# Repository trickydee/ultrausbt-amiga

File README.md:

# Amiga USB & Bluetooth Adapter

## Overview

This project uses a Raspberry Pi Pico to connect modern USB and Bluetooth devices such as keyboards, mice, trackballs and gamepads to classic Amiga computers — without needing a USB stack on the Amiga itself.

The project was created so I could connect my modern peripherals with my Amiga 2000, the device has a Keyboard and 2 x Atari style Joystick connectors to interface with the Amiga.

The example adapter hardware for the project is focused on the Amiga 2000, although it can be adapted easily for other Amigas.

The adapter is bi-directional:

* **Device Mode** (default): modern USB/Bluetooth HID → Amiga keyboard, mouse, joystick, and CD32 pad signalling
* **Host Mode**: real Amiga keyboard + Port 1 mouse + Port 2 Atari stick → USB HID keyboard/mouse/gamepad on a modern PC

Joystick/CD32 pads are supported toward the Amiga in Device Mode. In Host Mode, Port 2 accepts an Atari-style two-button stick as a USB HID gamepad (Mega Drive pads deferred — see [`doc/host-mode-port2-joystick.md`](./doc/host-mode-port2-joystick.md)).

The device is connected to the Amiga using straight through cables, I am using 2 x 9 Pin DSub to Dsub and 1 x 5 Pin DIN (MIDI) cables.

On a **Pico 2 W** you can mix USB and Bluetooth devices. USB-only builds work on any Pico / Pico 2.

**This project is a fork of [amigahid-pico](https://github.com/borb/amigahid-pico)** by **just nine** (borb). That project is the foundation for Amiga keyboard and mouse signalling on the Pico. This fork builds on that work for the ultrausbt Amiga Adapter board: OLED UI, dual joystick ports, CD32 pad protocol, Bluetooth (Bluepad32), many modern USB controllers, and USB **device** mode (Amiga keyboard/mouse → PC).

Please visit and star the upstream project:  
**https://github.com/borb/amigahid-pico**

Current test firmware: **v4.3.0** (shared Bluepad32 reconnect PR testing; not yet released) · [Release notes](./RELEASE_NOTES.md) · Architecture: [`doc/architecture.md`](./doc/architecture.md) · License: [EPL-2.0](./LICENSE) · [NOTICE](./NOTICE)

## Contributions

This project is open source and I am happy to receive pull requests and issues to further improve capabilities.

## USB device support

* USB HID Keyboards
* USB HID Mice
* USB HID Gamepads / Joysticks (see below)

## Game controller support

The following USB HID gamepads / joysticks are supported (more to come):

* PlayStation 3 DualShock 3 (and third-party PS3-compatible pads: HORI, Mad Catz, Qanba, Nacon, Logitech F310, etc.)
* PlayStation 4 DualShock 4 (and third-party PS4-compatible pads)
* PlayStation 5 DualSense and DualSense Edge (USB)
* PlayStation Classic (PSC)
* Xbox XInput — Xbox 360 / One / OG (plus HID fallback)
* Nintendo Switch Pro Controller, Joy-Con (L/R/Pair/Grip), SNES Controller (NSO)
* HORI HORIPAD for Nintendo Switch
* Google Stadia Controller

Other USB HID gamepads may work via the generic path (directions + up to three buttons). Gamepads map to **Joystick Port 2** by default; Port 1 can be switched to joystick / Llamatron / CD32 mode from the OLED or keyboard shortcuts.

## Bluetooth support (Pico 2 W)

Bluetooth keyboards, mice, and gamepads are supported on the **Raspberry Pi Pico 2 W** (RP2350) via [Bluepad32](https://github.com/ricardoquesada/bluepad32). You can run a fully wireless Amiga setup, or mix USB and Bluetooth devices.

### Pairing

1. On the OLED splash screen, hold **Middle + Left** (# + Up) to enable pairing (or wait for the short post-boot pairing window).
2. Put your device into Bluetooth pairing mode.
3. Confirm the device on the OLED **Devices** / **Map Devices** screens.

To clear stored pairing keys, open the OLED **Settings** page on the screen carousel (`#` from Map Devices), select **Clear BT pair**, confirm with `#`.

To turn pairing back on after it has timed out or been turned off: **Settings → Pair ON** (or **Middle + Left** / # + Up on Splash).

**Note:** Bluetooth support is intended for Pico 2 W. Prefer Pico 2 W for wireless builds.

# Usage

## USB

Connect devices to the Pico USB port (use a powered USB OTG hub if you need multiple devices). Supported keyboards, mice, and gamepads should enumerate within a few seconds; confirm on the OLED. If you find a modern device that does not work, open an issue.

## Bluetooth

See **Bluetooth support** above. Pairing is controlled from the OLED splash screen. Keyboard shortcuts work the same on USB and Bluetooth keyboards.

## Keyboard shortcuts

The adapter uses a number of Keyboard shortcut key combinations to toggle features.

These combos are handled by the adapter (USB **and** Bluetooth keyboards) and are **not** passed through to the Amiga. **Left Amiga** = Left Command / Left GUI / Left Windows on PC/Mac keyboards.

| Shortcut | Function |
|----------|----------|
| **Ctrl + Left Amiga + Right Amiga** | Amiga hard reset (classic) |
| **Ctrl + Left Amiga + Backspace** | Amiga hard reset (alternate for keyboards without Right Amiga/GUI) |
| **Shift + Left Amiga + J** | Toggle Port 1 between Amiga mouse and joystick |
| **Shift + Left Amiga + L** | Toggle Llamatron / Robotron style twin-stick mode (Port 2 move + Port 1 aim) |
| **Shift + Left Amiga + C** | Toggle Port 2 CD32 seven-button pad mode |

Port 1 full cycle (Ami Ms → Joy → CD32 → Llama → Atr Ms) is on the OLED **Left** button. Reset is signalled by holding the Amiga keyboard **CLOCK** line low (as a real Amiga keyboard MCU does), with a minimum hold time so it still works when a keyboard drops a combo key from its HID report.

Optional: remap one HID scancode to Amiga **Help** via `KEY_REMAP_HID_TO_HELP` in `src/config.h` (default: Logitech MX `| / ~ #` key). Set to `0` to disable. This is useful for mapping the quit key in WHDload.

### Llamatron dual-stick mode

**Shift + Left Amiga + L** enables Llamatron / twin-stick style routing (one dual-stick gamepad shared across ports: left stick → Port 2 move, right stick → Port 1 aim). Works with **Port 2 CD32** on; mutually exclusive with **Port 1 CD32**. See the OLED Port 1 mode label (**Llama**).

### CD32 seven-button mode

**CD32 pad emulation is complete and working** on both ports:

* **Port 2:** **Shift + Left Amiga + C**, or OLED **Right** (Joy ↔ CD32)
* **Port 1:** OLED **Left** cycle to **CD32** (Ami Ms → Joy → CD32 → Llama → Atr Ms)

Uses the Amiga CD32 serial pad protocol (seven buttons + D-pad). Compatible with Llamatron on Port 2 CD32; exclusive with Port 1 CD32. Protocol detail: [`doc/archive/CD32_BUILD_SPEC.md`](./doc/archive/CD32_BUILD_SPEC.md).

# OLED UI

An SSD1306 OLED and three buttons are supported on the ultrausbt Amiga board (optional for a bare Pico, but recommended). On modules with **Up / Down / #** keys: **Up** = Left, **Down** = Right, **#** = Middle.

The UI is a **screen carousel**: press **#** to advance pages (wraps to Splash).

| Mode | Carousel sequence |
|------|-------------------|
| **Device Mode** (USB/BT → Amiga) | Splash → Devices → Map Devices → Settings → Splash |
| **Host Mode** (Amiga kbd/mouse → PC) | Splash → Settings → Splash (Devices / Map Devices hidden) |

| Control | Action |
|---------|--------|
| **Left** (Up) | Splash/Devices: cycle Port 1 (Ami Ms → Joy → CD32 → Llama → Atr Ms). Settings: move cursor up |
| **Right** (Down) | Splash/Devices: cycle Port 2 (Joy ↔ CD32). Settings: move cursor down |
| **Middle** (#) | Advance screen carousel; on Settings: confirm selection |
| **Middle + Left** (# + Up) | Toggle Bluetooth pairing (Splash) |
| **Settings → Clear BT pair** | Clear stored Bluetooth pairing keys (`#` then confirm) |
| **Settings → Pair ON / Pair OFF** | Enable or disable Bluetooth pairing (label is the target state) |
| **Settings → Host Mode / Device Mode** | Switch to that role (`#` saves and reboots); label is the target, not current |
| **Settings → Back** | Return to Splash (default selection) |

Splash shows **Device Mode**, both ports in large type (`1:Ami Ms` / `2:Joy`), pairing status bottom-left, and firmware version bottom-right. **Ami Ms** = Amiga mouse, **Atr Ms** = Atari ST mouse pinout on Port 1.

OLED UX conventions (carousel, in-page select, confirms): [`doc/archive/oled-ui-style-guide.md`](./doc/archive/oled-ui-style-guide.md).

# USB Host Mode (Amiga keyboard / mouse / Port 2 stick on a PC)

The adapter can run in reverse: read a real Amiga keyboard (KCLK/KDAT), Port 1 mouse, and an **Atari-style two-button joystick on Port 2**, and present itself to a host PC (or MiSTer) as a composite USB HID keyboard + mouse + gamepad.

* Toggle from the OLED **Settings** carousel page (**Host Mode** / **Device Mode**); the board saves the role and reboots.
* In Host Mode the carousel is Splash ↔ Settings only.
* Port 2: straight DB-9 cable; directions + fire (pin 6) + button 2 (pin 9). No remapper needed for Atari sticks.
* Protocol and diagnostics: [`doc/archive/amiga-usb-device-mode.md`](./doc/archive/amiga-usb-device-mode.md). Research / future Mega Drive: [`doc/host-mode-port2-joystick.md`](./doc/host-mode-port2-joystick.md).

# Hardware

Note: The hardware adapter for this project is unique to this repo; the GPIOs differ from the original amigahid-pico adapters by nine/borb.

The [`kicad/`](./kicad/) directory includes an **Amiga 2000** reference board design and manufacturing gerbers (**Amiga 2000 Adapter v2.4**, `amiga-generic-dsub.*` + [`kicad/gerbers/`](./kicad/gerbers/)). More board designs will follow.

Firmware board maps:

* **Rev 5** — level-shifted Amiga I/O (`HIDPICO_REVISION=5` in root `CMakeLists.txt`)
* **Rev 6** — direct 5V-tolerant I/O on Pico 2 / Pico 2 W; Port 2 fire/B2/B3 on GPIO 16/17/18; OLED buttons on ADC 26/27/28 — see [`doc/gpio_rev6_adc_avoidance.md`](./doc/gpio_rev6_adc_avoidance.md)

Historical upstream PCB notes/errata (amigahid-pico / borb) remain in [`doc/archive/borb-amigahid-hardware.md`](./doc/archive/borb-amigahid-hardware.md) and [`doc/archive/borb-amigahid-errata.md`](./doc/archive/borb-amigahid-errata.md).

# Building the firmware

For the 4.3.0 shared Bluepad32 test build, see [local checkout testing](doc/bluepad32-local-testing.md).

The firmware can either be downloaded pre built from the Releases section, or you can build yourself with the 'build-all.sh' script. 

```bash
# Default: Pico 2 W → dist/
./build-all.sh

# Incremental rebuild
CLEAN_BUILD_DIRS=0 ./build-all.sh

# Multiple boards
BUILD_BOARDS=pico,pico2_w ./build.sh
BUILD_BOARDS=all ./build-all.sh
```

Flash the matching `.uf2` from `dist/` (hold **BOOTSEL**, copy to the RPI-RP2 drive).

Board revision is set in the root `CMakeLists.txt` (`HIDPICO_REVISION=5` or `6`).

By default the serial console shows boot info and device connect/disconnect messages. For verbose dumps, uncomment `DEBUG_MESSAGES=1` in `CMakeLists.txt`, or set `CONTROLLER_DEBUG` / `KEYBOARD_IN_DEBUG` in `src/config.h`.

# Documentation

Index: [`doc/README.md`](./doc/README.md)

| Doc | Topic |
|-----|--------|
| [`RELEASE_NOTES.md`](./RELEASE_NOTES.md) | Firmware changelog |
| [`doc/architecture.md`](./doc/architecture.md) | Architecture + developer/agent quickstart |
| [`doc/future_work.md`](./doc/future_work.md) | Known limitations / roadmap |
| [`doc/gpio_rev6_adc_avoidance.md`](./doc/gpio_rev6_adc_avoidance.md) | Rev 6 pin rationale |
| [`doc/BT_PAIRING_BEST_PRACTICES.md`](./doc/BT_PAIRING_BEST_PRACTICES.md) | Bluetooth pairing |
| [`doc/archive/`](./doc/archive/) | Detailed / historical notes |

# Acknowledgements

**Upstream — please support the original project:**

* **[amigahid-pico](https://github.com/borb/amigahid-pico)** by **just nine** \<[nine@aphlor.org](mailto:nine@aphlor.org)\> — the original Amiga HID-on-Pico work this firmware forks and extends. Without that project this adapter would not exist.

The “ultrausbt” name is tongue-in-cheek and highlights the capabilities made possible by TinyUSB, Bluepad32, and the Pico ecosystem.

This fork also relies on:

* [Raspberry Pi Pico SDK](https://github.com/raspberrypi/pico-sdk) — RP2040 / RP2350 platform
* [TinyUSB](https://github.com/hathach/tinyusb) by Ha Thach — USB host and device stacks
* [Bluepad32](https://github.com/ricardoquesada/bluepad32) by Ricardo Quesada — Bluetooth HID gamepads, keyboards, and mice
* [BTstack](https://github.com/bluekitchen/btstack) (via Pico SDK / Bluepad32) — Bluetooth controller stack
* [pico-ssd1306](https://github.com/daschr/pico-ssd1306) by David Schramm — OLED display driver
* [tusb_xinput](https://github.com/Ryzee119/tusb_xinput) by Ryzee119 — Xbox XInput host path for TinyUSB
* CD32 protocol analysis via [PSCD32 Development Diary](https://www.mrdictionary.net/PSCD32/diary/2019_08_09.htm) (Mathew Carr) and related pad schematics

**Other Projects**
I also have a number of other Retro Computer adapter projects:
[Atari Mega ST/TT IKBD - USB/BT Adapater](https://github.com/trickydee/ultrausbt-atari-st-rpikbd).
[Apple ADB - USB/BT Adapater](https://github.com/trickydee/ultrausbt-apple-adb-adapter).
[PC XT / AT / PS2 - USB/BT Adapater](https://github.com/trickydee/TBC).

**This ultrausbt Amiga fork** is maintained by [trickydee](https://github.com/trickydee) ([ultrausbt-amiga](https://github.com/trickydee/ultrausbt-amiga)). A large portion of the code and documentation was developed with [Cursor](https://cursor.com) and supporting LLMs — this project would not exist in its current form without those tools, on top of the open-source foundations above.

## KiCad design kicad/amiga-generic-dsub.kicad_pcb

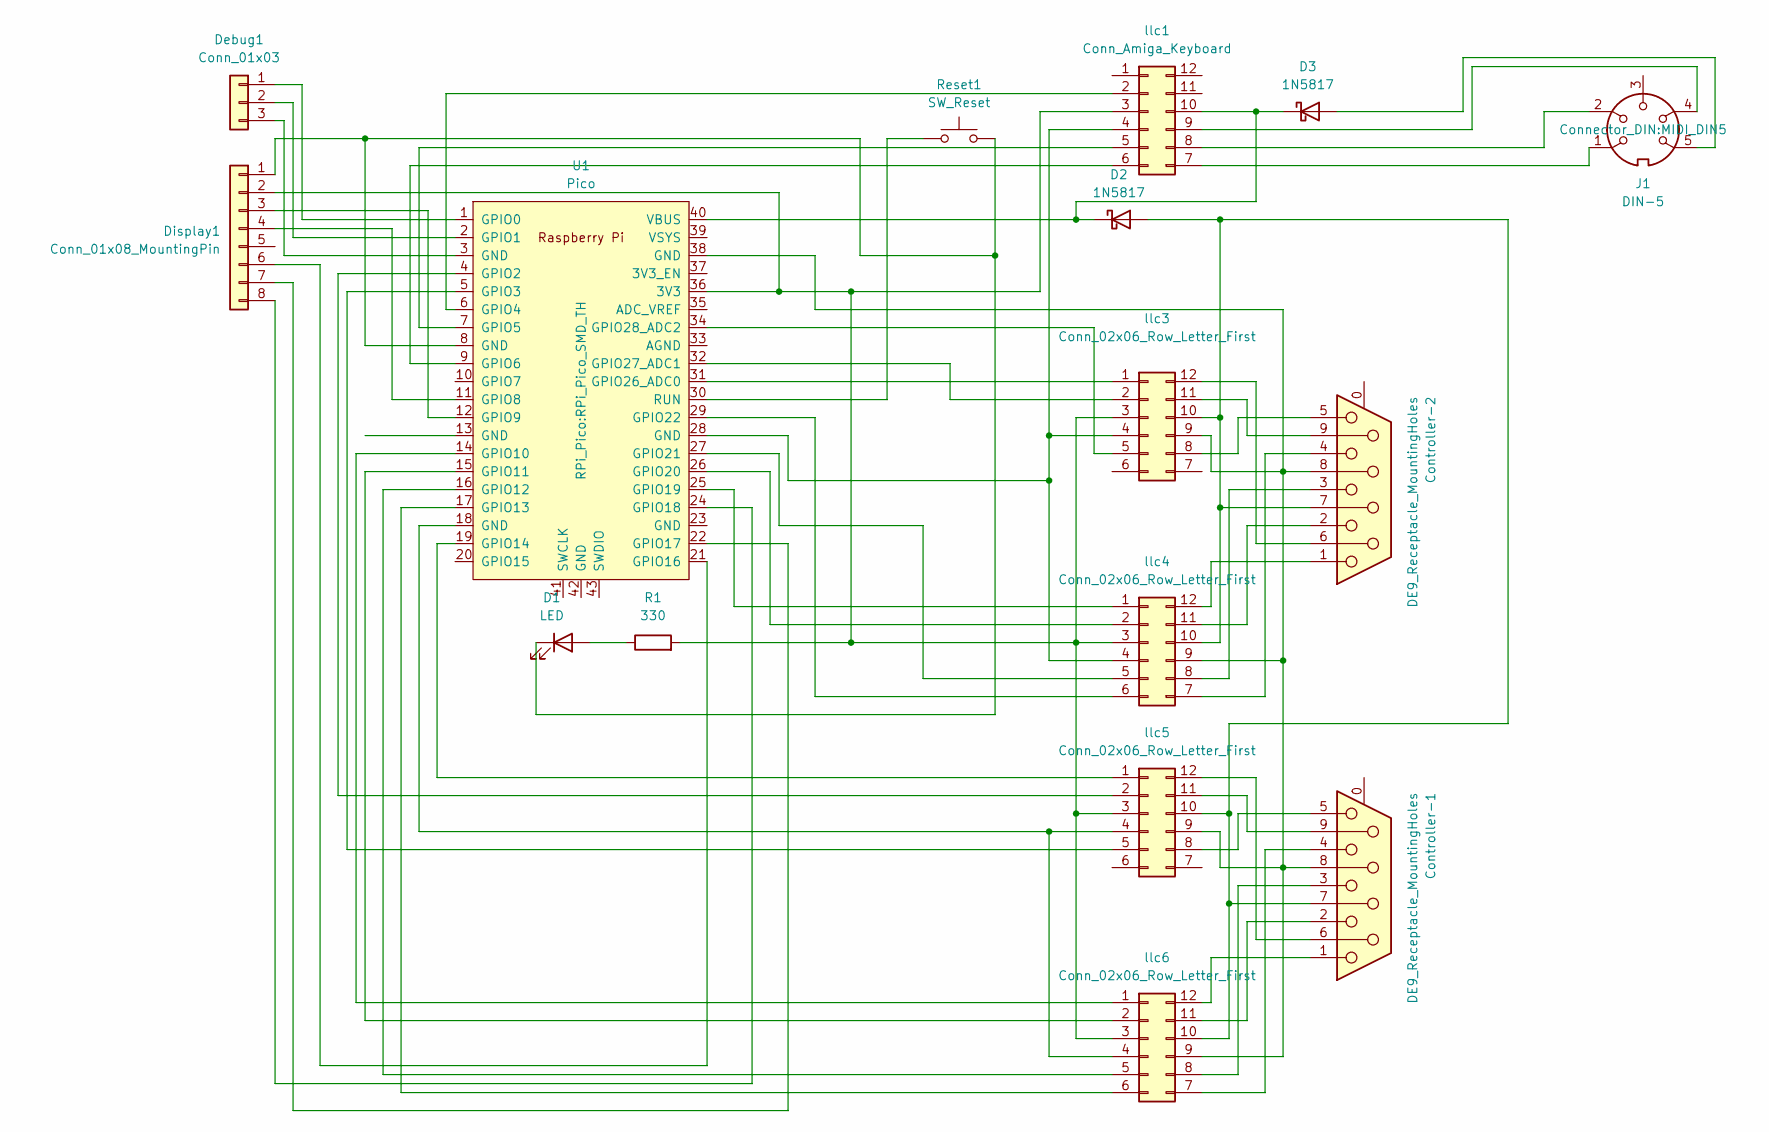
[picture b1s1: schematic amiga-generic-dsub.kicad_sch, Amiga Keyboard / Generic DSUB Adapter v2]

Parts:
Controller-1, Controller-2: DE9_Receptacle_MountingHoles; DSUB-9_Pins_Horizontal_P2.77x2.84mm_EdgePinOffset7.70mm_Hou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
D1: LED; LED_D3.0mm
D2, D3: 1N5817; D_DO-41_SOD81_P10.16mm_Horizontal
Debug1: Conn_01x03; PinSocket_1x03_P2.54mm_Vertical
Display1: Conn_01x08_MountingPin; PinSocket_1x08_P2.54mm_Vertical
J1: DIN-5; MIDI_DIN5
R1: 330; R_Axial_DIN0204_L3.6mm_D1.6mm_P7.62mm_Horizontal
Reset1: SW_Reset; SW_PUSH_6mm
U1: Pico; RPi_Pico_SMD_TH
llc1: Conn_Amiga_Keyboard; DIP-12_W10.16mm
llc3, llc4, llc5, llc6: Conn_02x06_Row_Letter_First; DIP-12_W10.16mm

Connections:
unnamed: D1.2 (A), R1.1
unnamed: D1.1 (K), Display1.1, Reset1.2, U1.8 (GND)
unnamed: Controller-1.7, Controller-2.7, D2.2 (A), llc3.10 (Pin_b3), llc4.10 (Pin_b3), llc5.10 (Pin_b3), llc6.10 (Pin_b3)
unnamed: D2.1 (K), D3.1 (K), U1.40 (VBUS), llc1.10 (Pin_b3)
unnamed: D3.2 (A), J1.5
unnamed: Debug1.1, U1.1 (GPIO0)
unnamed: Debug1.2, U1.2 (GPIO1)
unnamed: Debug1.3, U1.3 (GND)
unnamed: Display1.2, R1.2, U1.36 (3V3), llc1.3 (Pin_a3), llc3.3 (Pin_a3), llc4.3 (Pin_a3), llc5.3 (Pin_a3), llc6.3 (Pin_a3)
unnamed: Display1.3, U1.12 (GPIO9)
unnamed: Display1.4, U1.11 (GPIO8)
unnamed: Display1.6, U1.21 (GPIO16)
unnamed: Display1.7, U1.22 (GPIO17)
unnamed: Display1.8, U1.24 (GPIO18)
unnamed: U1.4 (GPIO2), llc5.2 (Pin_a2)
unnamed: U1.5 (GPIO3), llc5.5 (Pin_a5)
unnamed: U1.6 (GPIO4), llc1.2 (Pin_a2)
unnamed: U1.7 (GPIO5), llc1.5 (Pin_a5)
unnamed: U1.9 (GPIO6), llc1.6 (Pin_a6)
unnamed: U1.14 (GPIO10), llc6.1 (Pin_a1)
unnamed: U1.15 (GPIO11), llc6.2 (Pin_a2)
unnamed: U1.16 (GPIO12), llc6.5 (Pin_a5)
unnamed: U1.17 (GPIO13), llc6.6 (Pin_a6)
unnamed: U1.19 (GPIO14), llc5.1 (Pin_a1)
unnamed: U1.25 (GPIO19), llc4.1 (Pin_a1)
unnamed: U1.26 (GPIO20), llc4.2 (Pin_a2)
unnamed: U1.27 (GPIO21), llc4.5 (Pin_a5)
unnamed: U1.29 (GPIO22), llc4.6 (Pin_a6)
unnamed: U1.31 (GPIO26_ADC0), llc3.1 (Pin_a1)
unnamed: U1.32 (GPIO27_ADC1), llc3.2 (Pin_a2)
unnamed: U1.34 (GPIO28_ADC2), llc3.5 (Pin_a5)
unnamed: Reset1.1, U1.30 (RUN)
unnamed: U1.28 (GND), llc1.4 (Pin_a4), llc3.4 (Pin_a4), llc4.4 (Pin_a4)
unnamed: J1.4, llc1.9 (Pin_b4)
unnamed: J1.2, llc1.8 (Pin_b5)
unnamed: J1.1, llc1.7 (Pin_b6)
unnamed: Controller-2.6, llc3.12 (Pin_b1)
unnamed: Controller-2.9, llc3.11 (Pin_b2)
unnamed: Controller-1.8, Controller-2.8, U1.38 (GND), llc3.9 (Pin_b4), llc4.9 (Pin_b4), llc5.9 (Pin_b4), llc6.9 (Pin_b4)
unnamed: Controller-2.5, llc3.8 (Pin_b5)
unnamed: Controller-2.1, llc4.12 (Pin_b1)
unnamed: Controller-2.2, llc4.11 (Pin_b2)
unnamed: Controller-2.3, llc4.8 (Pin_b5)
unnamed: Controller-2.4, llc4.7 (Pin_b6)
unnamed: U1.18 (GND), llc5.4 (Pin_a4), llc6.4 (Pin_a4)
unnamed: Controller-1.6, llc5.12 (Pin_b1)
unnamed: Controller-1.9, llc5.11 (Pin_b2)
unnamed: Controller-1.5, llc5.8 (Pin_b5)
unnamed: Controller-1.1, llc6.12 (Pin_b1)
unnamed: Controller-1.2, llc6.11 (Pin_b2)
unnamed: Controller-1.3, llc6.8 (Pin_b5)
unnamed: Controller-1.4, llc6.7 (Pin_b6)

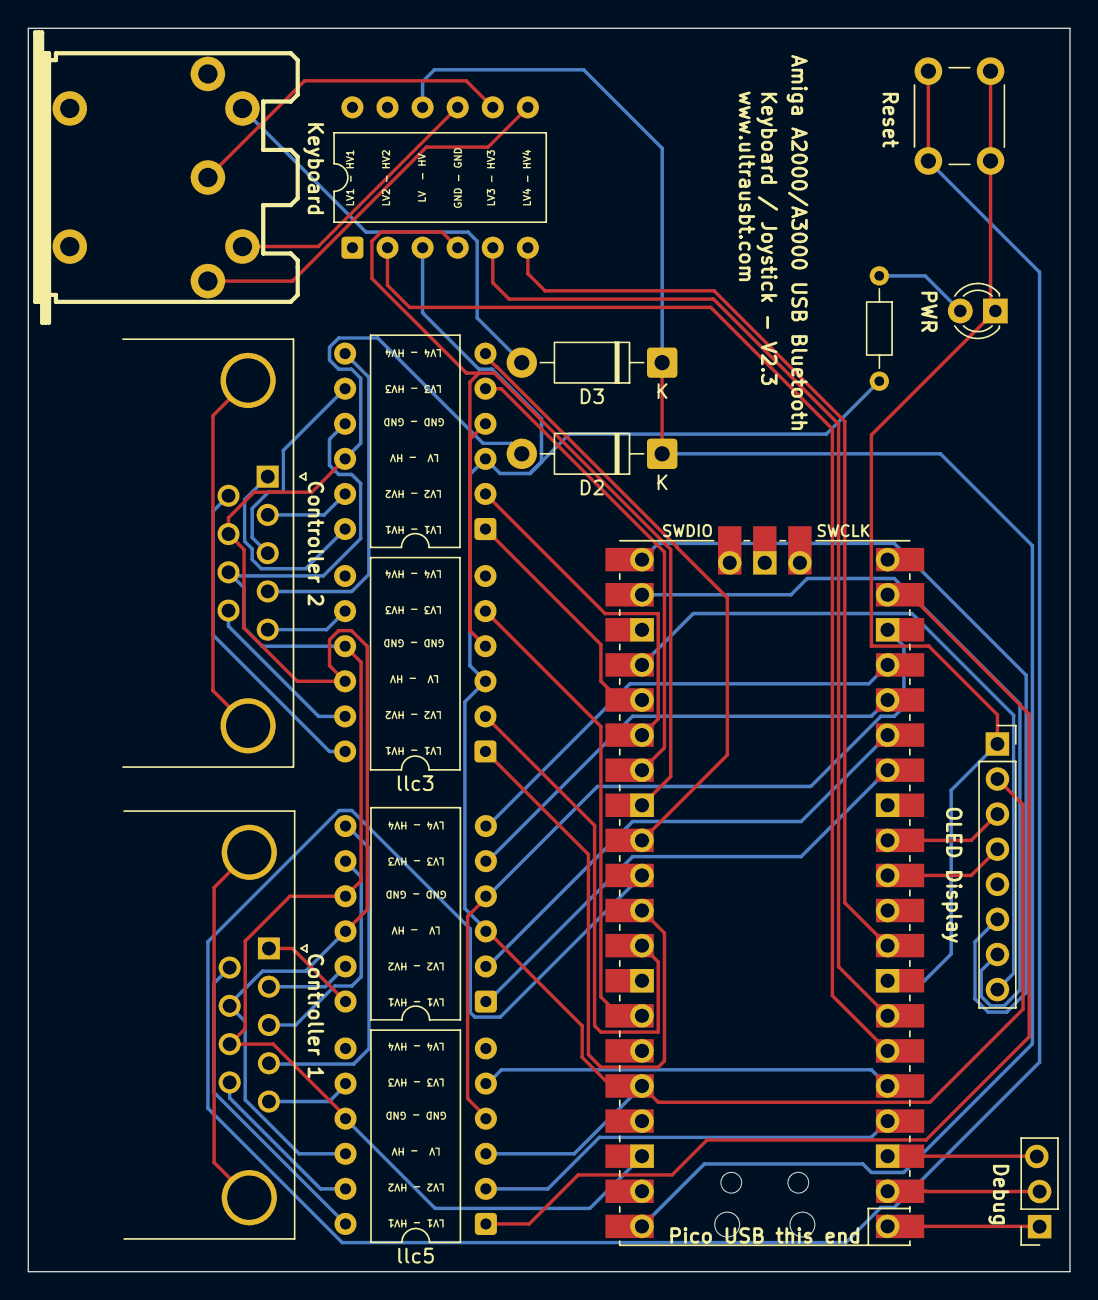
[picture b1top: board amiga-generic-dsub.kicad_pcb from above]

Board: 2 copper layers, 75.4 x 90.0 mm, 16 parts (0 on the bottom side), 52 nets.

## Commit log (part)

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2026-01-12 Update Pico SDK to 2.2.0 and improve build system
    - Update pico-sdk submodule to version 2.2.0 (fixes CMake 4.x compatibility)
    - Fix linker error: add extern to disp_write function pointer declaration
    - Configure build to output UF2 file to build/ instead of build/src/
    - Add build.sh script for automated building with submodule initialization
2026-01-13 Add dual-platform build support and update TinyUSB to 0.20.0
    - Update build.sh to build for both Pico (RP2040) and Pico 2 W (RP2350)
    - Use separate build directories: build/ for RP2040, build-pico2w/ for RP2350
    - Update tinyusb submodule to version 0.20.0 (latest release)
    - Add build summary showing both platform builds
2026-01-13 Update .gitignore and submodules
    - Update .gitignore to exclude build directories and CMake artifacts
    - Update tinyusb submodule to latest commit (a71cb2364)
    - Ensure pico-sdk and bluepad32 submodules are properly configured
    Build directories (build/, build-*), CMake files, and submodule directories
    are now properly excluded from version control.
2026-01-13 Add USB mouse to joystick port 1 support
    - Created joystick_port1.c/h for joystick port 1 GPIO control
    - Maps USB mouse movement to joystick directions (with threshold)
    - Maps USB mouse buttons to joystick buttons:
    - Left button -> Fire
    - Right button -> Button 2
    - Middle button -> Button 3
2026-01-13 Add joystick port 1 DB-9 pin to GPIO mapping documentation
    - Added doc/joystick_port1_pinout.md with detailed DB-9 pin to GPIO mapping table
    - Documents Revision 4 GPIO assignments for joystick port 1
    - Includes signal names, GPIO pins, descriptions, and active states
    - References KiCad schematic netlist for accurate pin mappings
2026-01-15 Add 200MHz overclock support and migrate to tusb_init()
    - Add 200MHz overclock for all Pico boards (pico, pico_w, pico2_w)
    - Configure manual PLL settings for Pico 2 W (RP2350) at 200MHz
    - Migrate from deprecated tuh_init() to tusb_init() with proper structure
    - Add performance optimization documentation
    - Add TinyUSB migration guide documentation
    All boards now run at 200MHz for improved performance. USB devices
2026-01-15 Add build scripts for all supported boards
    - Add build-all.sh to build for Pico, Pico W, and Pico 2 W
    - Add build-pico2w.sh for Pico 2 W only builds
    - Add .DS_Store to .gitignore
2026-01-19 Swap LEFT and DOWN GPIO mappings for joystick port 2
    - Swapped GPIO mappings to match documented pinout
    - DOWN: GPIO 22 -> GPIO 26 (QM2_AMIGA_VQ -> QM2_AMIGA_H)
    - LEFT: GPIO 26 -> GPIO 22 (QM2_AMIGA_H -> QM2_AMIGA_VQ)
    - Updated comments to reflect correct pinout
    - Build verified for both Pico (RP2040) and Pico 2 W (RP2350)
2026-01-19 Optimize main loop and GPIO operations, fix analog stick calibration
    Main loop optimizations:
    - Add batched process_bluepad32_devices() function
    - Early returns when no Bluetooth devices connected
    - Reduces function call overhead in main loop
    GPIO optimizations:
    - Create shared gpio_util.c/h with direction state caching
2026-01-19 Remove debug printf and migrate all GPIO functions to shared utility
    Performance optimizations:
    - Remove debug printf statements from gamepad hot path (usb_hid.c)
    - Migrate joystick_port1.c to use shared gpio_util functions
    - Migrate quad_mouse.c to use shared gpio_util functions
    - Migrate keyboard_serial_io.c to use shared gpio_util functions
    Code quality improvements:
2026-01-19 Improve mouse processing with speed-proportional timing
    Implement time-based quadrature generation based on Atari code:
    - Add speed-proportional timing: faster movement = shorter period = more responsive
    - Use time-based updates instead of fixed delays for better CPU efficiency
    - Add motion accumulation to handle rapid updates smoothly
    - Reduce MIN_PERIOD_US to 200us and MAX_SPEED to 30000 for better fast movement
    - Remove period recalculation during motion to prevent instability and skip-back
2026-01-19 Add Llamatron twinstick mode support
    - Add Shift + Left Amiga + L toggle for Llamatron mode
    - Left stick controls Port 2 (movement), right stick controls Port 1 (fire direction)
    - Auto-activates joystick mode on port 1 when enabling Llamatron
    - Restores previous port 1 mode (mouse/joystick) when disabling Llamatron
    - Only active when exactly one gamepad is connected
    - Fire buttons: BUTTON_B for Port 2, BUTTON_A for Port 1
2026-01-26 Add documentation for GPIO allocation, electrical operation, and troubleshooting
    - Add GPIO allocation plan for Atari/Amiga dual compatibility
    - Add electrical operation documentation explaining 3.3V to 5V interface
    - Add troubleshooting guide for intermittent mouse/joystick failures
    - Document power supply considerations and GPIO initialization issues
2026-01-26 Add multi-keyboard support for Bluetooth keyboards
    - Process all connected Bluetooth keyboards (up to 2)
    - Merge input from all keyboards (modifiers: OR logic, keys: union)
    - Toggle key combinations (Port 1 mode, Llamatron mode) only processed from first keyboard
    - Deduplicate keys when multiple keyboards press the same key
    - Maintains backward compatibility with single keyboard usage
2026-01-27 Add GPIO clearing at startup and watchdog functionality
    - Add GPIO reset to INPUT state at startup (100ms delay + reset)
    - Add lightweight watchdog that checks GPIO state every 5 seconds
    - Watchdog detects stuck GPIOs and recovers by resetting to INPUT
    - Move GPIO reset message to after dbgcons_init() so it's visible
    - Add documentation for GPIO fix and watchdog functionality
    - Add OLED display library analysis document
2026-01-28 Fix joystick port 1 LEFT/RIGHT movement and button conflicts
    - Fix GPIO direction setting: Always set GPIO direction regardless of cache state
    This ensures GPIOs are correctly configured even if mouse code changed them
    - Add memory barriers for cross-core synchronization between joystick and mouse code
    - Disable Button 2/3 in joystick mode to prevent conflicts with LEFT/RIGHT directions
    (Button 2 uses GPIO 12 = LEFT, Button 3 uses GPIO 13 = RIGHT)
    - Add memory barriers in mouse quadrature code when checking joystick mode
2026-01-28 Add third display screen for Bluetooth device names and joystick mode toggle
    - Add DISPLAY_SCREEN_BT_NAMES screen showing first 2 joysticks, first keyboard, and first mouse
    - Add bluepad32_get_device_name() function to retrieve Bluetooth device names
    - Store device names in storage structures when devices are ready
    - Update button handling:
    - LEFT button on devices screen: toggle joystick port 1 mode (mouse/joystick)
    - MIDDLE button: cycle through 3 screens (SPLASH -> DEVICES -> BT_NAMES -> SPLASH)
2026-01-28 Use direct access to bluepad32 device structure fields
    - Access device name directly from d->name (no need to store separately)
    - Use uni_bt_conn_get_address() to get device address for name matching
    - Use d->controller_type for Xbox controller detection (more reliable)
    - Keep vendor/product ID check for Stadia (mapped to AndroidController)
    - Simplify device name storage by matching discovered names by address
    - Remove unnecessary pending name storage by device pointer
2026-01-30 Remove debug logging and update splash screen (v1.0.11)
    - Remove all debug logging (GPIO-UTIL, JOY2-FIRE, JOY2-INIT, JOY2-RESET, GAMEPAD-DEBUG)
    - Document debug logging in doc/debug_logging_removed.md
    - Update splash screen branding: 'amigahid-pico' -> 'ultramegausb.com'
    - Fix mode indicator: Show 'USB+BT' when both USB and BT devices are connected
    - Ensure RST label is displayed when Bluetooth is enabled
    - Auto-refresh splash screen when BT device counts change
2026-02-01 Fix button 2/3 handling and watchdog coverage
    - Added buttons 2 and 3 to watchdog sample (GPIOs 2, 3, 27, 28)
    - Fixed misleading comment in joystick_port2.c (GPIO 27 is Button 2, not UP)
    - Added Port 2 buttons 2 and 3 support in Llamatron mode
    - Removed Port 2 gamepad -> Port 1 mouse button mapping (Port 2 only controls Port 2)
    - Fixed mouse/gamepad button handling to only update on state changes (reduces log spam)
    - Added debug logging for mouse button GPIO state changes
2026-02-02 Remap Port 2 Button 2 to GPIO 7 and add debug logging (v1.0.25)
    - Remap QM2_AMIGA_B2 from GPIO 27 (ADC1) to GPIO 7 (non-ADC)
    - Fixes high LOW voltage (397mV) issue on GPIO 27
    - GPIO 7 is non-ADC, should provide proper LOW voltage
    - Add debug logging for button 2/3 troubleshooting
    - Port 1 buttons 2/3: Added printf logging
    - Port 2 buttons 2/3: Enhanced logging with GPIO numbers
2026-02-02 Remove D-pad UP filter - GPIO conflict was the root cause
    - Removed D-pad UP filter that was masking a GPIO conflict issue
    - Simplified CONVERT_GAMEPAD_TO_DIRECTIONS macro
    - GPIO conflicts have been resolved, filter no longer needed
    - Bump version to 1.0.31
    - UP+FIRE now works correctly on both joystick ports
2026-02-03 Add Atari mouse mode toggle and fix Bluetooth screen
    - Added mouse type enum (MOUSE_TYPE_AMIGA, MOUSE_TYPE_ATARI) to quad_mouse.h
    - Implemented mouse type toggle functions with GPIO pin swapping for Atari mode
    - Atari mode swaps GPIO pins 1 and 4 (V and HQ) on DB-9 connector
    - Added mouse type display on devices screen when Port 1 is in mouse mode
    - Added RIGHT button handler to toggle mouse type on devices screen
    - Added "Bluetooth Devices" title to Bluetooth screen (page 3)
2026-02-03 Remove debug messages for joystick and mouse buttons
    - Removed [JOY1-B2] and [JOY1-B3] debug messages from joystick port 1
    - Removed [JOY2-B2] and [JOY2-B3] debug messages from joystick port 2
    - Removed [MOUSE-BTN] debug messages from mouse button handler
    - Removed [system] debug output from debug console counters
    - Removed [amigak] debug output from keyboard debug console
    - Cleaned up unused variables in mouse button function
2026-02-05 Update splash screen to show mouse type and refresh after flash load
    - Splash screen now displays 'ATARI' or 'AMIGA' based on current mouse type
    - Refresh splash screen after mouse type is loaded from flash on startup
    - This ensures correct title is shown immediately on boot
    - Bump version to 1.0.36
2026-02-05 Update splash screen to show Port 1 mode and change LEFT button function
    - Splash screen title now shows current Port 1 mode:
    - AMIGA/ATARI when in mouse mode (based on mouse type)
    - JOYSTICK when in joystick mode
    - LLAMA when in llamatron mode (shortened from LLAMATRON)
    - Adjusted positioning: JOYSTICK moved left (x=5), LLAMA centered (x=25)
    - Changed LEFT button on splash screen to cycle Port 1 modes:
2026-02-09 Swap Port 2 Button 2 back to GPIO 27 and bump version to 1.0.37
    - Revert QM2_AMIGA_B2 from GPIO 7 back to GPIO 27 (ADC1)
    - Bump version from 1.0.36 to 1.0.37
2026-02-24 Add Switch 0x200E/0x2017, PSC and HORI HORIPAD drivers; README and v1.0.54
    - Switch: add JoyCon Charge Grip (0x200E) and SNES NSO (0x2017) to VID/PID check
    - PlayStation Classic: new driver (0x054C/0x0CDA), d-pad and face/shoulder to port 2
    - HORI HORIPAD: new driver (0x0F0D/0x00C1), d-pad/stick and B/A/Y to port 2
    - README: supported controllers table and release notes for v1.0.54
    - config.h: bump SOFTWARE_VERSION_PATCH to 54
2026-05-07 Add timed startup pairing window and live splash countdown.
    Enable pairing for 60 seconds after boot before auto-locking it off, show remaining seconds on the splash Pair status line, refresh the splash once per second while countdown is active, and bump firm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
2026-05-07 Document pairing UX updates and bump release to v2.1.0.
    Add release notes for splash pairing toggle, 60-second startup pairing window, key-clear hold workflow, and live countdown refresh; update firmware version macros to 2.1.0.

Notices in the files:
kicad/amiga-generic-dsub.kicad_sch:
(c) 2026
